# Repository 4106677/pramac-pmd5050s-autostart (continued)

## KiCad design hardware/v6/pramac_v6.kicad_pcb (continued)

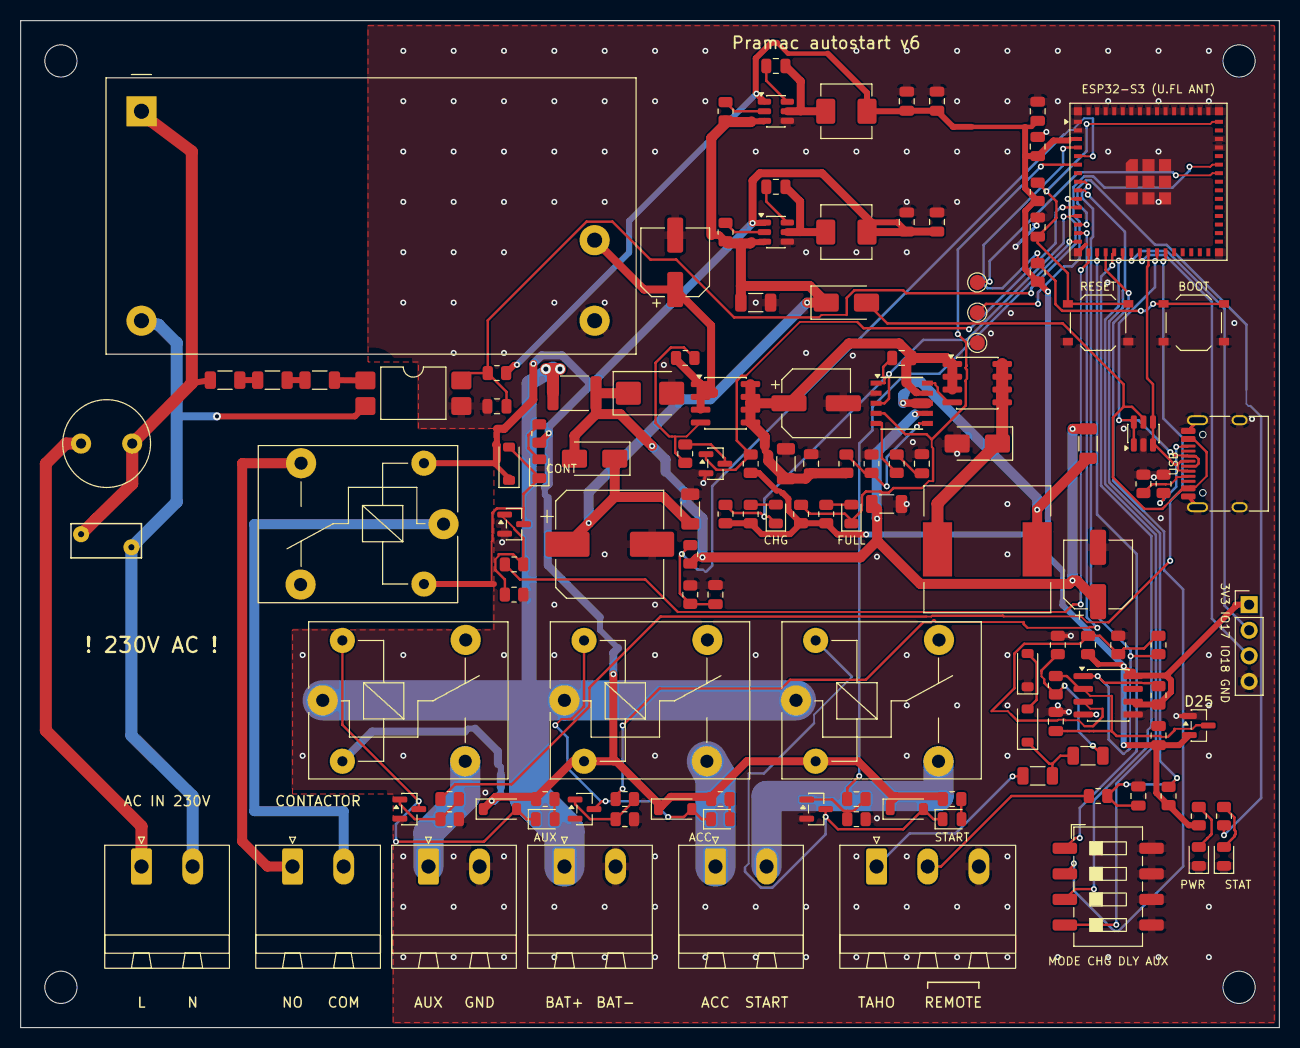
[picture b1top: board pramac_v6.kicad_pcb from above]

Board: 2 copper layers, 125.0 x 100.0 mm, 134 parts (0 on the bottom side), 84 nets.

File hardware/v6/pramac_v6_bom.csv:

Comment,Designator,Footprint,LCSC,Qty
470u 35V,C1,CP_Elec_10x10.5,C2836436,1
10u 50V X5R,"C2,C13,C61,C66",C_1206_3216Metric,C13585,4
100n 50V X7R,"C3,C4,C7,C10,C31,C32,C62,C63",C_0805_2012Metric,C49678,8
22u 10V X5R,"C5,C6,C8,C9,C12",C_0805_2012Metric,C380338,5
1u 25V X7R,"C11,C41",C_0805_2012Metric,C89190,2
10u 25V X7R,C30,C_1206_3216Metric,C70462,1
10n 50V X7R,C33,C_0805_2012Metric,C1710,1
100u 35V,"C40,C60,C65",CP_Elec_6.3x7.7,C2836442,3
220n 50V X7R,C64,C_0805_2012Metric,C5378,1
SMBJ18A,D1,D_SMB,C353379,1
SS54,"D2,D22",D_SMA,C22452,2
SS34,D4,D_SMA,C8678,1
1N4148W,"D10,D11,D12,D16",D_SOD-123,C81598,4
LED ACC,D13,LED_0805_2012Metric,C84256,1
LED START,D14,LED_0805_2012Metric,C84256,1
LED CONTACTOR,D15,LED_0805_2012Metric,C84256,1
LED AUX,D17,LED_0805_2012Metric,C84256,1
BZT52C5V1,"D20,D21",D_SOD-123,C2117,2
LED CHARGING,D23,LED_0805_2012Metric,C84256,1
LED CHARGED,D24,LED_0805_2012Metric,C2297,1
BAV99,D25,SOT-23,C2500,1
LED POWER,D30,LED_0805_2012Metric,C2297,1
LED STATUS,D31,LED_0805_2012Metric,C2297,1
PTC 2A hold 1812,F1,Fuse_1812_4532Metric,C434887,1
T1A 250VAC TR5,F2,Fuse_Littelfuse_372_D8.50mm,C142808,1
AC IN 230V (L N),J1,"PhoenixContact_MSTBA_2,5_2-G-5,08_1x02_P5.08mm_Horizontal",C3697,1
CONTACTOR (NO COM),J2,"PhoenixContact_MSTBA_2,5_2-G-5,08_1x02_P5.08mm_Horizontal",C3697,1
BATTERY (+ -),J3,"PhoenixContact_MSTBA_2,5_2-G-5,08_1x02_P5.08mm_Horizontal",C3697,1
ACC START,J4,"PhoenixContact_MSTBA_2,5_2-G-5,08_1x02_P5.08mm_Horizontal",C3697,1
TAHO REMOTE REMOTE,J5,"PhoenixContact_MSTBA_2,5_3-G-5,08_1x03_P5.08mm_Horizontal",C8377,1
TYPE-C-31-M-12,J6,USB_C_Receptacle_HRO_TYPE-C-31-M-12,C165948,1
SPARE 3V3 IO17 IO18 GND,J7,PinHeader_1x04_P2.54mm_Vertical,C2691448,1
AUX (OUT GND),J8,"PhoenixContact_MSTBA_2,5_2-G-5,08_1x02_P5.08mm_Horizontal",C3697,1
SRD-05VDC-SL-C,"K1,K2,K3,K4",Relay_SPDT_SANYOU_SRD_Series_Form_C,C35449,4
4.7u 5A FXL0530,"L1,L2",L_Changjiang_FXL0530,C177246,2
47u 2.5A SMDRI127,L20,L_12x12mm_H8mm,C9906,1
IRM-20-24,PS1,Converter_ACDC_MeanWell_IRM-20-xx_THT,C194964,1
AO3400A,"Q1,Q2,Q3,Q4,Q22",SOT-23,C20917,5
AO4421,"Q20,Q21",SOIC-8_3.9x4.9mm_P1.27mm,C33484,2
100k,"R1,R3,R8,R11,R13,R15,R17,R34,R62",R_0805_2012Metric,C149504,9
22k,"R2,R32",R_0805_2012Metric,C17560,2
10k,"R4,R5,R31,R33,R37,R38,R60,R61,R64,R67,R69",R_0805_2012Metric,C17414,11
5k1,"R6,R7",R_0805_2012Metric,C27834,2
100,"R10,R12,R14,R16",R_0805_2012Metric,C17408,4
2k2,"R20,R21,R22,R23",R_0805_2012Metric,C17520,4
22k,R30,R_1206_3216Metric,C25830,1
4k7,R35,R_0805_2012Metric,C17673,1
1k,"R36,R50,R51,R68,R70",R_0805_2012Metric,C17513,5
47k,"R40,R41,R42",R_1206_3216Metric,C25833,3
47k,R43,R_0805_2012Metric,C17713,1
150k,R63,R_0805_2012Metric,C17470,1
120,R65,R_0805_2012Metric,C17437,1
0.12 1% 1206,R66,R_1206_3216Metric,C2907346,1
07D471K,RV1,RV_Disc_D7mm_W3.4mm_P5mm,C28756,1
RESET,SW1,SW_Push_1P1T_XKB_TS-1187A,C318884,1
BOOT,SW2,SW_Push_1P1T_XKB_TS-1187A,C318884,1
DIP switch 4P,SW3,SW_DIP_SPSTx04_Slide_6.7x11.72mm_W8.61mm_P2.54mm_LowProfile,C6331176,1
ESP32-S3-MINI-1U-N8,U1,ESP32-S2-MINI-1U,C2980299,1
AP63203WU-7,U2,TSOT-23-6,C780769,1
AP63205WU-7,U3,TSOT-23-6,C2071056,1
USBLC6-2SC6,U4,SOT-23-6,C7519,1
LM393DR2G,U5,SOIC-8_3.9x4.9mm_P1.27mm,C7955,1
LTV-814S-TA1-A,U6,SMDIP-4_W9.53mm,C108051,1
CN3767,U20,SSOP-10_3.9x4.9mm_P1.00mm,C81968,1
"WJ2EDGK-5.08-02P-14-00A (loose, not soldered: plug 2P for J1-J4, J8)",,,C71370,5
"WJ2EDGK-5.08-03P-14-00A (loose, not soldered: plug 3P for J5)",,,C71371,1

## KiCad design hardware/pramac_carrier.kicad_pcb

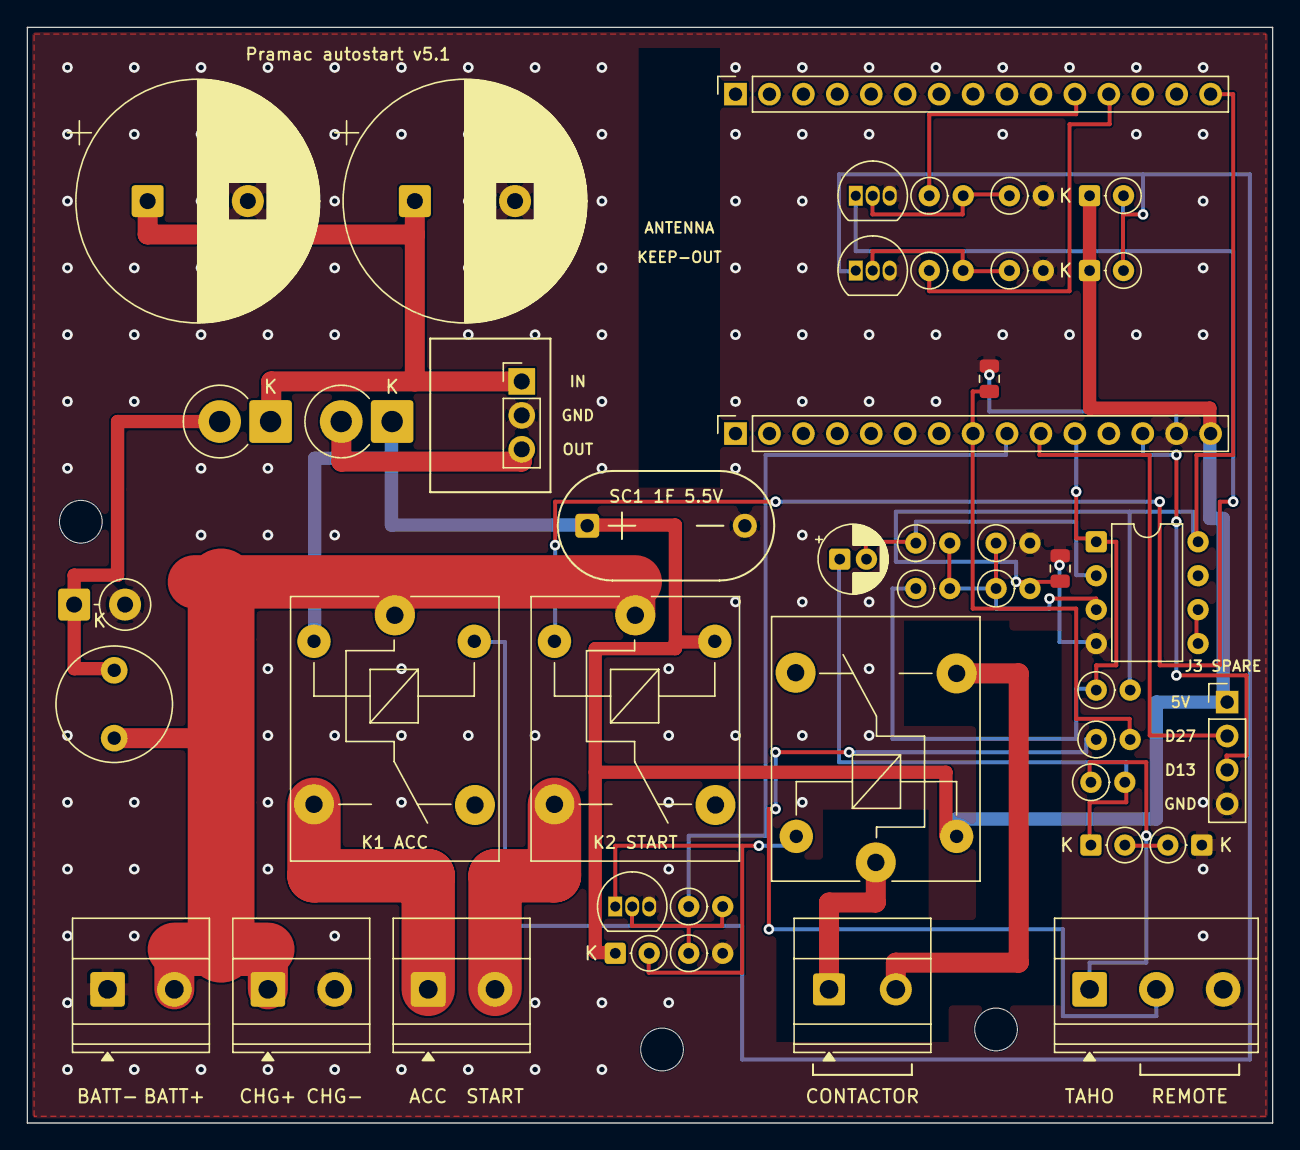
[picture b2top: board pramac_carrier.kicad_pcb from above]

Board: 2 copper layers, 93.2 x 82.0 mm, 47 parts (0 on the bottom side), 31 nets.

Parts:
C1, C2: 4700u 25V; CP_Radial_D18.0mm_P7.50mm
C3: 10u 16V NP; CP_Radial_D5.0mm_P2.00mm
C5, C6: 100n; C_0805_2012Metric
D1, D2: 1N5821; D_DO-201AD_P3.81mm_Vertical_CathodeUp
D3: P6KE36A (P6KE20A recommended); D_DO-15_P3.81mm_Vertical_CathodeUp
D4, D5: BZX55C5V1; D_DO-35_SOD27_P2.54mm_Vertical_CathodeUp
D6, D7, D8: 1N4148; D_DO-35_SOD27_P2.54mm_Vertical_CathodeUp
F1: KLS5-102-5RT-020H 2A slow; Fuse_Littelfuse_372_D8.50mm
H1, H2, H3: M3; MountingHole_3.2mm_M3
J1: BATT- / BATT+; TerminalBlock_Phoenix_MKDS-1,5-2_1x02_P5.00mm_Horizontal
J2: TAHO / REMOTE; TerminalBlock_Phoenix_MKDS-1,5-3_1x03_P5.00mm_Horizontal
J3: Spare relay module 5V/IN1(D27)/IN2(D13)/GND; PinHeader_1x04_P2.54mm_Vertical
J4: CHARGER +12V / GND; TerminalBlock_Phoenix_MKDS-1,5-2_1x02_P5.00mm_Horizontal
J5: ACC OUT / START OUT (relay NO); TerminalBlock_Phoenix_MKDS-1,5-2_1x02_P5.00mm_Horizontal
J6: CONTACTOR (relay K3 dry COM/NO, 230V); TerminalBlock_Phoenix_MKDS-1,5-2_1x02_P5.00mm_Horizontal
K1: SRD-05VDC-SL-A ACC; Relay_SPDT_SANYOU_SRD_Series_Form_C
K2: SRD-05VDC-SL-A START; Relay_SPDT_SANYOU_SRD_Series_Form_C
K3: SRD-05VDC-SL-A CONTACTOR; Relay_SPDT_SANYOU_SRD_Series_Form_C
Q1, Q2, Q3: BC337; TO-92_Inline
R1: 22k; R_Axial_DIN0207_L6.3mm_D2.5mm_P2.54mm_Vertical
R4: 100k; R_Axial_DIN0207_L6.3mm_D2.5mm_P2.54mm_Vertical
R5: 4.7k; R_Axial_DIN0207_L6.3mm_D2.5mm_P2.54mm_Vertical
R6: 1k; R_Axial_DIN0207_L6.3mm_D2.5mm_P2.54mm_Vertical
RM1: Favotek RM20S-050 SIP-3: 1 +VIN, 2 GND, 3 +VOUT; PinHeader_1x03_P2.54mm_Vertical
Rb1, Rb2: 1k; R_Axial_DIN0207_L6.3mm_D2.5mm_P2.54mm_Vertical
Rb3: 10k; R_Axial_DIN0207_L6.3mm_D2.5mm_P2.54mm_Vertical
Rg3: 1k; R_Axial_DIN0207_L6.3mm_D2.5mm_P2.54mm_Vertical
Rp1, Rp2, Rp3: 10k; R_Axial_DIN0207_L6.3mm_D2.5mm_P2.54mm_Vertical
Rv1, Rv2: 10k; R_Axial_DIN0207_L6.3mm_D2.5mm_P2.54mm_Vertical
SC1: JEC SMD05R5S0001DARZ 1F 5.5V; CP_Radial_D5.0mm_P2.00mm
U1A: ESP32 bottom row; PinSocket_1x15_P2.54mm_Vertical
U1B: ESP32 top row; PinSocket_1x15_P2.54mm_Vertical
U3: LM393 (soldered, no socket); DIP-8_W7.62mm

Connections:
3V3: C5.1, R5.2, Rv1.2, U1B.15, U3.8
ACC: Rb1.1, U1B.12
ACC_OUT: J5.1, K1.3
BASE_ACC: Q1.2, Rb1.2, Rp1.1
BASE_CONT: Q3.2, Rg3.2, Rp3.1
BASE_START: Q2.2, Rb2.2, Rp2.1
CMP_OUT: R4.1, R5.1, U1A.11, U3.1
COIL_ACC: D6.2, K1.5, Q1.1
COIL_CONT: D8.2, K3.5, Q3.1
COIL_START: D7.2, K2.2, Q2.1
CONT: Rg3.1, U1A.9
CONTACT: J2.2, R6.1
CT_COM: J6.1, K3.1
CT_NO: J6.2, K3.3
D25: C6.1, R6.2, U1A.8
EXT1: J3.2, U1A.10
EXT2: J3.3, U1A.13
GND: C1.2, C2.2, C5.2, C6.2, D3.2, D5.1, J1.1, J2.3, J3.4, J4.2, Q1.3, Q2.3, Q3.3, RM1.2, Rp1.2, Rp2.2, Rp3.2, Rv2.2, SC1.2, U1A.14, U3.4
NODE_A: C1.1, C2.1, D1.1, RM1.1
NODE_B: D2.1, D6.1, D7.1, D8.1, J3.1, K1.2, K2.5, K3.2, SC1.1, U1A.15
START: Rb2.1, U1B.11
START_OUT: J5.2, K2.3
TAHO_AC: C3.2, Rb3.1, U3.2
TAHO_CL: C3.1, D4.1, R1.2
TAHO_IN: J2.1, R1.1
UNUSED_IN: U3.5, U3.6
VB: R4.2, Rb3.2, Rv1.1, Rv2.1, U3.3
VBATT: F1.1, J1.2, J4.1, K1.1, K2.1
VBF: D1.2, D3.1, F1.2
VBUCK: D2.2, RM1.3
ZMID: D4.2, D5.2

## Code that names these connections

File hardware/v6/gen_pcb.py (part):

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    track(board, nets, "AC_LF", F, [f2b, (17, 36), (17, 13), (ps1l[0] + 1, ps1l[1] + 1), ps1l], MW)
    rv1a, rv1b = p("RV1", 1), p("RV1", 2)
    track(board, nets, "AC_LF", F, [f2b, (f2b[0], 46), (rv1a[0] + 1.5, rv1a[1] - 1.5), rv1a], MW)
    # detector chain under the AC-DC module: AC_LF -> R40 -> R41 -> R42 -> U6 pin 1; AC_N to U6 pin 2 (via from the bottom)
    track(board, nets, "AC_LF", F, [(17, 36), p("R40", 1)], 0.6)
    for a, b, n in (("R40", "R41", "AC_D1"), ("R41", "R42", "AC_D2"), ("R42", "U6", "AC_D3")):
        track(board, nets, n, F, [p(a, 2), p(b, 1)], 0.6)
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    for ref, n, lab in [("J1", 1, "L"), ("J1", 2, "N"), ("J2", 1, "NO"), ("J2", 2, "COM"), ("J3", 1, "BAT+"), ("J3", 2, "BAT-"),
                        ("J4", 1, "ACC"), ("J4", 2, "START"), ("J8", 1, "AUX"), ("J8", 2, "GND"), ("J5", 1, "TAHO")]:
        text(lab, pin(ref, n)[0], LY, 1.0)
    # REMOTE: dry contact across J5 pins 2 and 3 (polarity does not matter), one label with a bracket over both pins
    r2, r3 = pin("J5", 2)[0], pin("J5", 3)[0]
    for a_, b_ in (((r2, LY - 2.0), (r2, LY - 1.4)), ((r2, LY - 2.0), (r3, LY - 2.0)), ((r3, LY - 2.0), (r3, LY - 1.4))):
        s = pcbnew.PCB_SHAPE(board); s.SetShape(pcbnew.SHAPE_T_SEGMENT); s.SetLayer(pcbnew.F_SilkS); s.SetWidth(FromMM(0.15))
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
